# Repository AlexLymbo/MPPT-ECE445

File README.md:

# Senior Design Project(ECE445) - Custom Illini Solar Car MPPT
This project contains both the HW and FW for a boost converter MPPT made for the 3rd generation vehicle of Illini Solar Car. It utilizes a simple perturb and observe algorithm (P&O).

## More Info: 
The goal of this project was to develop custom and low cost solar Maximum Power Point Trackers (MPPTs). These MPPTs use a boost converter to optimize power output from the solar array to charge the battery efficiently. With the array divided into three sections for reliability, each MPPT gives redundancy to the system. Customization gives simple integration with the vehicle's electrical systems, allowing for plug-and-play functionality. This cost-effective solution takes away the need for expensive off-the-shelf components and provides access to schematics for easy maintenance and upgrades. 

https://www.youtube.com/watch?v=uG63rXX1FN4&t=2s

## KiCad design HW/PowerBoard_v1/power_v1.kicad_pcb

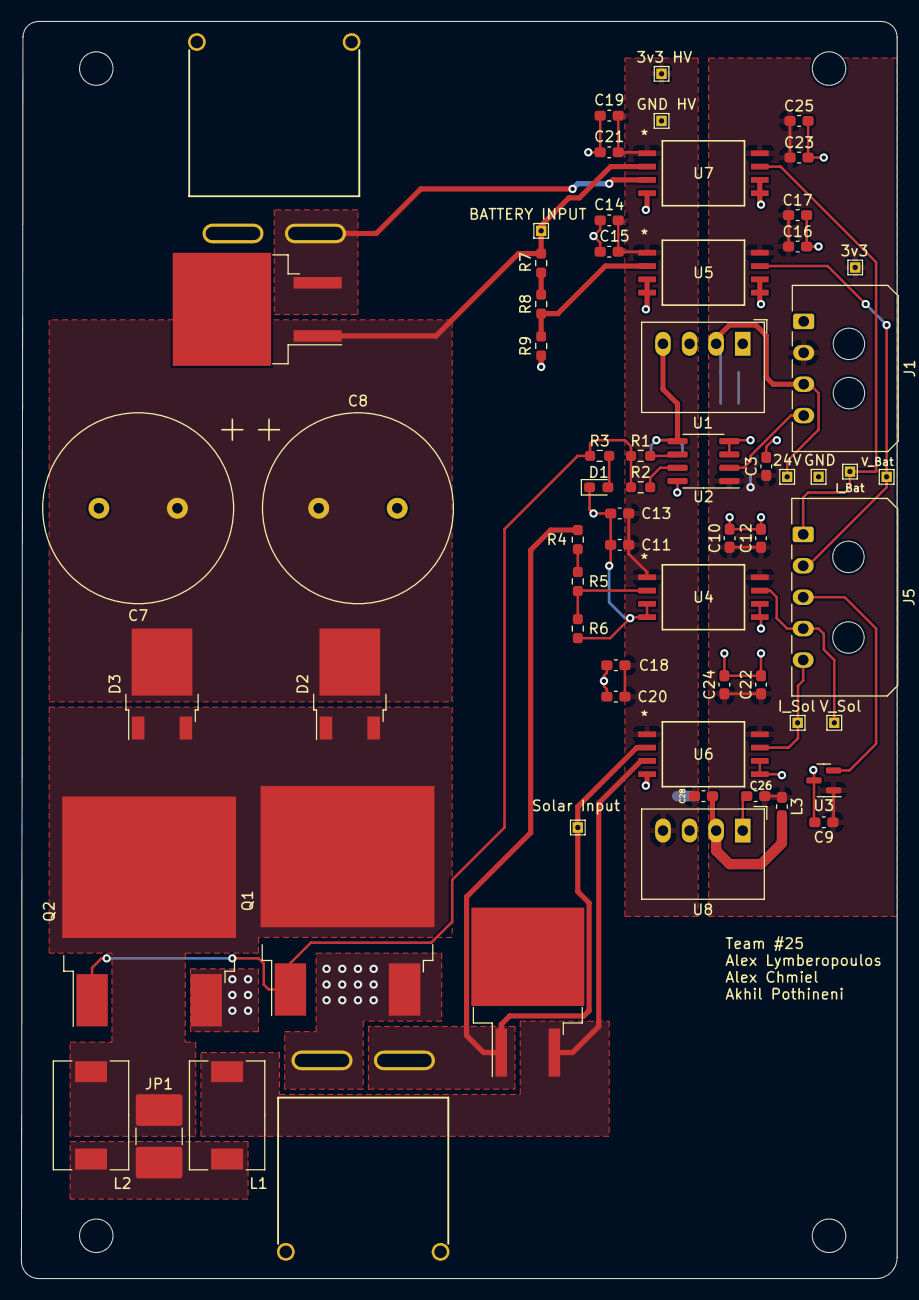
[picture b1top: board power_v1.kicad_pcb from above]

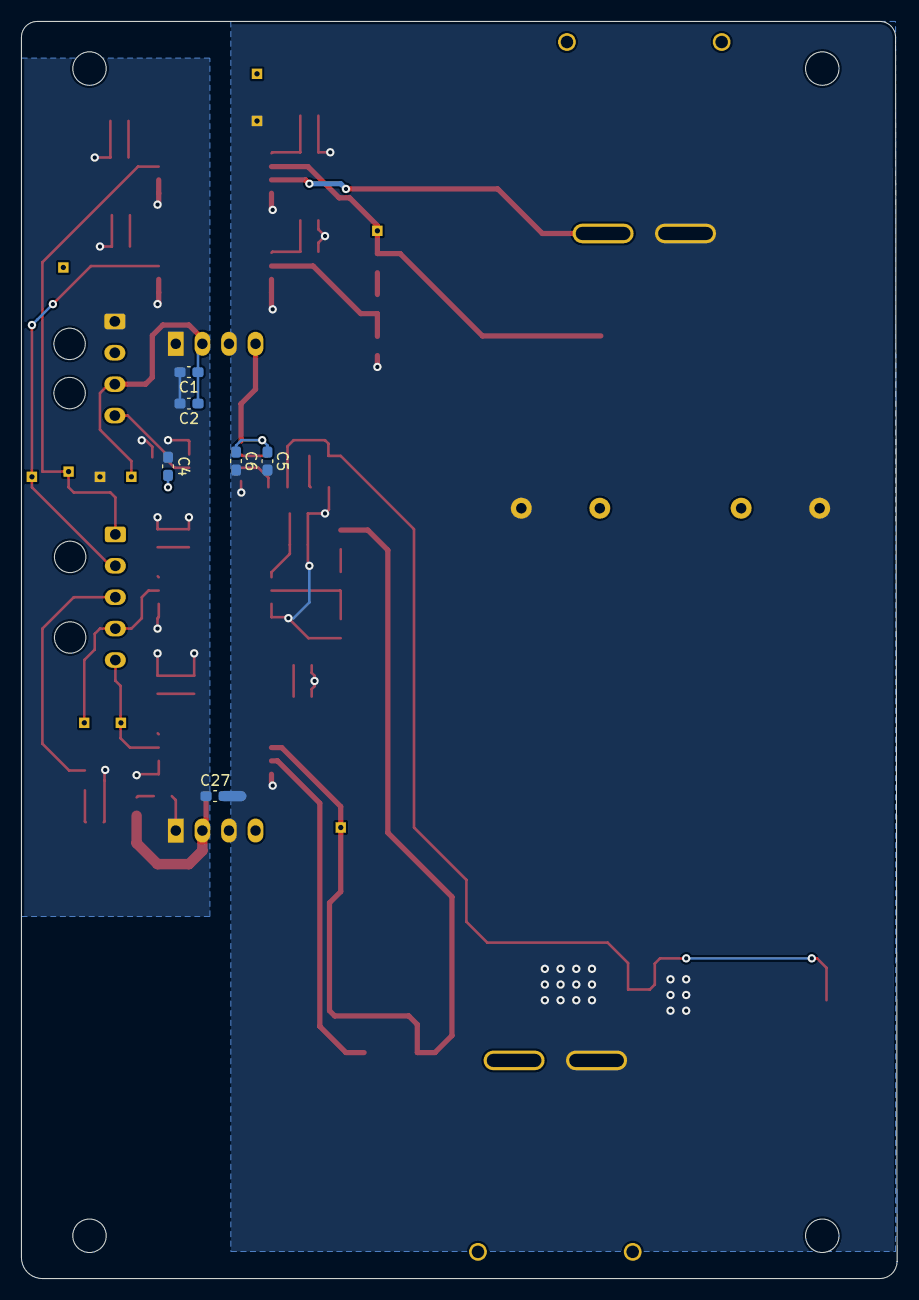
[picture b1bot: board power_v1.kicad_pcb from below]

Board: 2 copper layers, 83.6 x 120.1 mm, 75 parts (6 on the bottom side), 27 nets.

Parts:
C1, C26: 10uF; C_0603_1608Metric_Pad1.08x0.95mm_HandSolder
C2, C28: 1nF; C_0603_1608Metric_Pad1.08x0.95mm_HandSolder
C3, C4, C5, C6, C12, C13, C14, C17, C18, C19, C24, C25: 1uF; C_0603_1608Metric_Pad1.08x0.95mm_HandSolder
C7, C8: 470uF; C_Radial_D18.0mm_H35.5mm_P7.50mm
C9: 0.1uF; C_0603_1608Metric_Pad1.08x0.95mm_HandSolder
C10, C11, C15, C16, C20, C21, C22, C23: 100nF; C_0603_1608Metric_Pad1.08x0.95mm_HandSolder
C27: 2.2nF; C_0603_1608Metric_Pad1.08x0.95mm_HandSolder
D1: Blue; LED_0603_1608Metric_Pad1.05x0.95mm_HandSolder
D2, D3: 0.83V; TO-252-2
H1, H2, H3, H4: MountingHole; MountingHole_3.2mm_M3
J1: Inputs; Molex_Micro-Fit_3.0_43650-0400_1x04_P3.00mm_Horizontal
J3: Vin Solar; Anderson_Powerpole_45A_1x2_Horizontal_Bottom
J4: Vout Battery; Anderson_Powerpole_45A_1x2_Horizontal_Bottom
J5: Sensors; Molex_Micro-Fit_3.0_43650-0500_1x05_P3.00mm_Horizontal
JP1: SolderJumper_2_Open; R_2816_7142Metric
L1, L2: 1.2 μH; L_Wuerth_HCM-1050
L3: 22uH; L_0603_1608Metric_Pad1.05x0.95mm_HandSolder
Q1, Q2: IXTT220N20X4HV; TO-268-2
R1: 10; R_0603_1608Metric_Pad0.98x0.95mm_HandSolder
R2: 0; R_0603_1608Metric_Pad0.98x0.95mm_HandSolder
R3: 10k; R_0603_1608Metric_Pad0.98x0.95mm_HandSolder
R4, R5, R7, R8: 500k; R_0603_1608Metric_Pad0.98x0.95mm_HandSolder
R6: 53k; R_0603_1608Metric_Pad0.98x0.95mm_HandSolder
R9: 41.7k; R_0603_1608Metric_Pad0.98x0.95mm_HandSolder
R10, R11: 0.75; TO-263-2_isolatedback
TP1: +3V3A; TestPoint_THTPad_1.0x1.0mm_Drill0.5mm
TP2: GNDA; TestPoint_THTPad_1.0x1.0mm_Drill0.5mm
TP3: 24V; TestPoint_THTPad_1.0x1.0mm_Drill0.5mm
TP4: GND; TestPoint_THTPad_1.0x1.0mm_Drill0.5mm
TP5: 3V3; TestPoint_THTPad_1.0x1.0mm_Drill0.5mm
TP6: ADC V Sol; TestPoint_THTPad_1.0x1.0mm_Drill0.5mm
TP7, TP11: ADC V Batt; TestPoint_THTPad_1.0x1.0mm_Drill0.5mm
TP8: ADC I Sol; TestPoint_THTPad_1.0x1.0mm_Drill0.5mm
TP9, TP13: ADC I Batt; TestPoint_THTPad_1.0x1.0mm_Drill0.5mm
U1: RO-2412S; Converter_DCDC_RECOM_R-78S-0.1_THT
U2: STGAP2SMTR; SOIC-8_3.9x4.9mm_P1.27mm
U3: MCP9700AT-ETT; SOT-23
U4, U5, U6, U7: PAMC1350DWVR; U_PAMC1350DWVR_TEX
U8: 3v3 ISO DC/DC; Converter_DCDC_RECOM_R-78S-0.1_THT

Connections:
+3.3VA: C11.1, C13.1, C14.1, C15.1, C18.1, C19.1, C20.1, C21.1, C28.1, TP1.1, U4.1 (VDD1), U5.1 (VDD1), U6.1 (VDD1), U7.1 (VDD1), U8.4 (+VOUT)
+3V3: C3.1, C4.1, C9.1, C10.1, C12.1, C16.1, C17.1, C22.1, C23.1, C24.1, C25.1, C26.1, J1.2, L3.1, TP5.1, U2.1 (VDD), U3.1 (Vdd), U4.8 (VDD2), U5.8 (VDD2), U6.8 (VDD2), U7.8 (VDD2)
+24V: C1.1, C2.1, J1.3, TP3.1, U1.2 (+VIN)
/ADC I Batt: J5.1, TP9.1, U7.7 (OUTP)
/ADC I Sol: J5.5, TP8.1, U6.7 (OUTP)
/ADC V Batt: J5.2, TP7.1, U5.7 (OUTP)
/ADC V Sol: J5.4, TP6.1, U4.7 (OUTP)
/Batt In: C7.1, C8.1, D2.2 (K), D3.2 (K), R7.1, R11.1, TP11.1, U7.2 (INP)
/Batt Out: J4.1, R11.2, U7.3 (INN)
/Board Temp: J5.3, U3.2 (Vout)
/DNP Anode: D2.1 (A), D2.3 (A), D3.1 (A), D3.3 (A), JP1.2 (B), L2.2, Q1.2 (D), Q2.2 (D)
/Gate: Q1.1 (G), Q2.1 (G), R1.1, R2.1, R3.1
/PWM: J1.4, U2.2 (IN+)
/SW_G+: R1.2, U2.6 (GON)
/SW_G-: R2.2, U2.7 (GOFF)
/Sensors/V Sense Batt: R8.2, R9.1, U5.2 (INP)
/Sensors/V Sense Sol: R5.2, R6.1, U4.2 (INP)
/Sol In: J3.2, R4.1, R10.1, TP13.1, U6.2 (INP)
/Sol Out: L1.1, R10.2, U6.3 (INN)
Earth: C5.2, C6.2, C7.2, C8.2, C11.2, C13.2, C14.2, C15.2, C18.2, C19.2, C20.2, C21.2, C27.2, D1.1 (K), J3.1, J4.2, Q1.3 (S), Q2.3 (S), R6.2, R9.2, TP2.1, U1.3 (-VOUT), U2.8 (GNDISO), U4.3 (INN), U4.4 (GND1), U5.3 (INN), U5.4 (GND1), U6.4 (GND1), U7.4 (GND1), U8.3 (-VOUT)
GND: C1.2, C2.2, C3.2, C4.2, C9.2, C10.2, C12.2, C16.2, C17.2, C22.2, C23.2, C24.2, C25.2, C26.2, C27.1, J1.1, TP4.1, U1.1 (-VIN), U2.3 (IN-), U2.4 (GND), U3.3 (GND), U4.5 (GND2), U4.6 (OUTN), U5.5 (GND2), U5.6 (OUTN), U6.5 (GND2), U6.6 (OUTN), U7.5 (GND2), U7.6 (OUTN), U8.1 (-VIN)
unnamed: D1.2 (A), R3.2
unnamed: JP1.1 (A), L1.2, L2.1
unnamed: R4.2, R5.1
unnamed: R7.2, R8.1
unnamed: C5.1, C6.1, U1.4 (+VOUT), U2.5 (VH)
unnamed: C28.2, L3.2, U8.2 (+VIN)

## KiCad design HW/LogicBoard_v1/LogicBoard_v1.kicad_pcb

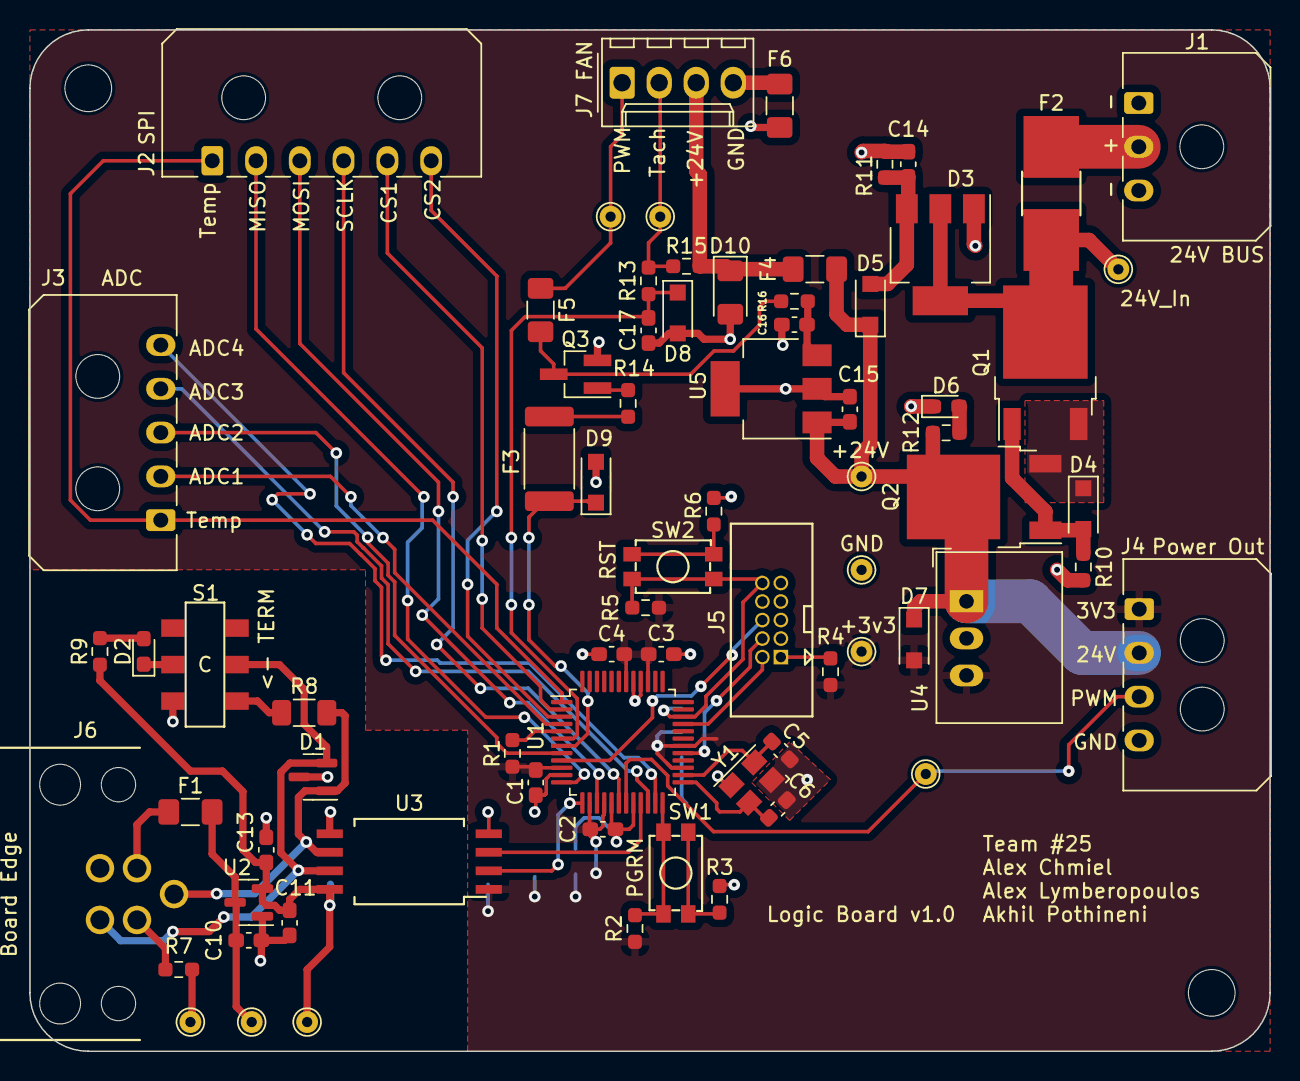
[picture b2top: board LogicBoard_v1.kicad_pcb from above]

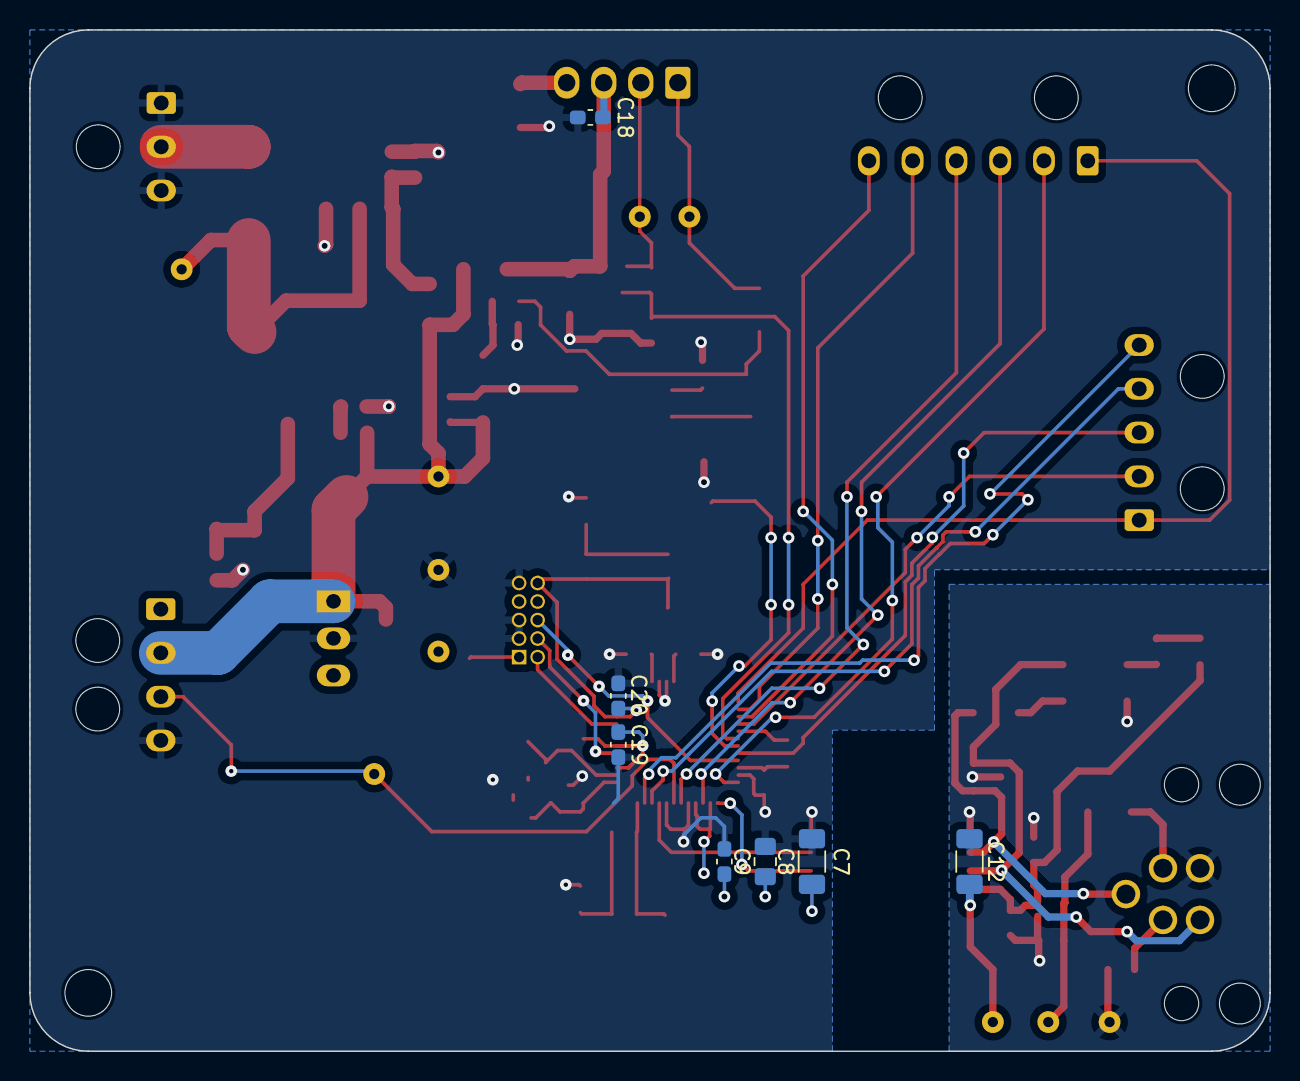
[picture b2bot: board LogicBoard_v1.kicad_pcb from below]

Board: 2 copper layers, 85.0 x 70.0 mm, 83 parts (7 on the bottom side), 53 nets.

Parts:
C1, C2, C3, C4, C9, C10, C11, C13, C15, C17, C19, C20: 0.1uF; C_0603_1608Metric_Pad1.08x0.95mm_HandSolder
C5, C6: 18pF; C_0603_1608Metric_Pad1.08x0.95mm_HandSolder
C7, C12: 10uF; C_1206_3216Metric_Pad1.33x1.80mm_HandSolder
C8: 1uF; C_0805_2012Metric_Pad1.18x1.45mm_HandSolder
C14: 0.047u; C_0603_1608Metric_Pad1.08x0.95mm_HandSolder
C16: 10uF; C_0603_1608Metric_Pad1.08x0.95mm_HandSolder
C18: 1uF; C_0603_1608Metric_Pad1.08x0.95mm_HandSolder
D1: PESD1CAN; SOT-23
D2: Yellow; LED_0603_1608Metric_Pad1.05x0.95mm_HandSolder
D3: Q_SCR_KAG; SOT-223-3_TabPin2
D4: 20 V; D_SOD-123F
D5: 28 V; D_SOD-123F
D6: LED; LED_0603_1608Metric_Pad1.05x0.95mm_HandSolder
D7: D_Schottky; D_SOD-123F
D8, D9: 3V6; D_SOD-123F
D10: 40V 2A; D_1206_3216Metric_Pad1.42x1.75mm_HandSolder
F1: 0.2A; Fuse_1206_3216Metric_Pad1.42x1.75mm_HandSolder
F2: 5A; Littelfuse_154_4.24mm_x_3.81mm
F3: 100mA; Fuse_2512_6332Metric
F4: 0.25A Fuse; Fuse_1206_3216Metric_Pad1.42x1.75mm_HandSolder
F5: 0.2A Fuse; Fuse_1206_3216Metric_Pad1.42x1.75mm_HandSolder
F6: 1A Fuse; Fuse_1206_3216Metric_Pad1.42x1.75mm_HandSolder
H1, H2: MountingHole; MountingHole_3.2mm_M3
J1: 24V In; Molex_Micro-Fit_3.0_43650-0300_1x03_P3.00mm_Horizontal
J2: Comm; Molex_Micro-Fit_3.0_43650-0600_1x06_P3.00mm_Horizontal
J3: ADC; Molex_Micro-Fit_3.0_43650-0500_1x05_P3.00mm_Horizontal
J4: Power; Molex_Micro-Fit_3.0_43650-0400_1x04_P3.00mm_Horizontal
J5: JTAG_Header; IDC-Header_2x05_Pitch1.27mm_Straight
J6: CAN; M12_5-pin_90deg_VertPitch2.54mm
J7: Fans; Molex_KK-254_AE-6410-04A_1x04_P2.54mm_Vertical
Q1, Q2: Q_PMOS_GDS; TO-252-2
Q3: Q_NMOS_GSD; SOT-23_Handsoldering
R1, R2, R5, R11, R12, R13, R15: 10k; R_0603_1608Metric_Pad0.98x0.95mm_HandSolder
R3, R6, R9, R10: 1k; R_0603_1608Metric_Pad0.98x0.95mm_HandSolder
R4: 0; R_0603_1608Metric_Pad0.98x0.95mm_HandSolder
R7: 1M; R_0603_1608Metric_Pad0.98x0.95mm_HandSolder
R8: 120; R_1206_3216Metric_Pad1.30x1.75mm_HandSolder
R14: 500; R_0603_1608Metric_Pad0.98x0.95mm_HandSolder
R16: 10K; R_0603_1608Metric_Pad0.98x0.95mm_HandSolder
S1: CL-SB-22B-01; DPDT_NIDEC_6_pin_SMD_1.6_x_1.2_pads
SW1: ISP; Button_223AM
SW2: ~RESET; Button_223AM
TP1: Duty PWM; TestPoint_THTPad_D1.5mm_Drill0.7mm
TP2: CAN_VCC_Fused; TestPoint_THTPad_D1.5mm_Drill0.7mm
TP3: GND_CAN; TestPoint_THTPad_D1.5mm_Drill0.7mm
TP4: +5V_CAN; TestPoint_THTPad_D1.5mm_Drill0.7mm
TP5: 24V IN; TestPoint_THTPad_D1.5mm_Drill0.7mm
TP6: GND; TestPoint_THTPad_D1.5mm_Drill0.7mm
TP7: 24V OUT; TestPoint_THTPad_D1.5mm_Drill0.7mm
TP8: 3v3; TestPoint_THTPad_D1.5mm_Drill0.7mm
TP9: Tach; TestPoint_THTPad_D1.5mm_Drill0.7mm
TP10: Fan PWM; TestPoint_THTPad_D1.5mm_Drill0.7mm
U1: LPC1547JBD48; LQFP-48_7x7mm_P0.5mm
U2: MCP1754S-5002E_SOT23A; SOT-23
U3: ISO1042DWV; SOIC-8_5.85x7.4mm_P1.27mm
U4: R-783.3-0.5; Converter_DCDC_RECOM_R-78E-0.5_THT
U5: BD450M2FP3-CE2; SOT-223-3_TabPin2
Y1: 12MHz; Crystal_SMD_TXC_7M-4pin_3.2x2.5mm

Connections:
+3V3: C1.1, C2.1, C3.1, C4.1, C7.1, C8.1, C9.1, C19.1, D7.2 (A), J4.1, R1.1, R2.1, R4.1, R5.2, TP8.1, U1.10 (VREFP_ADC), U1.14 (VREFP_DAC_VDDCMP), U1.16 (VDDA), U1.27 (VDD), U1.30 (VBAT), U1.39 (VDD), U1.42 (VDD), U3.1 (Vcc1), U4.3 (OUT)
+5V: C16.1, R16.1, U5.3 (VO)
+24V: C15.1, D5.1 (K), D7.1 (K), F4.1, J4.2, Q2.2 (D), R12.1, TP7.1, U4.1 (IN), U5.1 (VI)
/CAN/+5V_CAN: C11.1, C12.1, C13.1, R9.2, TP4.1, U2.2 (VO), U3.8 (Vcc2)
/CAN/CANH: D1.2 (K), J6.4, S1.5, U3.7 (CANH)
/CAN/CANL: D1.1 (K), J6.5, R8.2, U3.6 (CANL)
/CAN/CAN_RX: U1.21 (PIO0_13/ADC1_6), U3.3 (RXD)
/CAN/CAN_Shield: J6.1, R7.2
/CAN/CAN_TX: U1.13 (PIO0_18/SCT0_OUT5), U3.2 (TXD)
/CAN/CAN_VCC_Fused: C10.1, F1.1, TP2.1, U2.3 (VI)
/CAN/CAN_VCC_Unfused: F1.2, J6.2
/CAN/GND_CAN: C10.2, C11.2, C12.2, C13.2, D1.3 (A), J6.3, R7.1, S1.3, TP3.1, U2.1 (GND), U3.5 (GND2)
/CAN/TERM_LED: D2.1 (K), S1.2
/Fans/24V_fused: C18.1, D10.1 (K), F4.2, J7.3, R15.1
/Fans/Fan_PWM: D9.1 (K), F3.2, U1.7 (PIO0_6/ADC0_2/SCT2_OUT3)
/Fans/Fan_Tach: C17.2, D8.1 (K), R13.1, U1.6 (PIO0_5/ADC0_3)
/Fans/PWM_5V: F5.2, Q3.3 (D), R16.2
/Fans/Tach: J7.2, R13.2, R15.2, TP9.1
/MCU/ADC_1: J3.2, U1.4 (PIO0_3/ADC0_5/SCT1_OUT4)
/MCU/ADC_2: J3.3, U1.8 (PIO0_7/ADC0_1)
/MCU/ADC_3: J3.4, U1.22 (PIO0_14/ADC1_7/SCT1_OUT5)
/MCU/ADC_4: J3.5, U1.23 (PIO0_15/ADC1_8)
/MCU/CS_1: J2.5, U1.2 (PIO0_1/ADC0_7/SCT0_OUT4)
/MCU/CS_2: J2.6, U1.3 (PIO0_2/ADC0_6/SCT1_OUT3)
/MCU/ISP0: R1.2, U1.5 (PIO0_4/ADC0_4)
/MCU/ISP1: R2.2, SW1.1, U1.24 (PIO0_16/ADC1_9)
/MCU/MISO: J2.2, U1.12 (PIO0_9/ADC1_1/TDI)
/MCU/MOSI: J2.3, U1.15 (PIO0_10/ADC1_2)
/MCU/PWM: J4.3, TP1.1, U1.19 (PIO0_12/DAC_OUT)
/MCU/RESET: C20.1, J5.10 (~RESET), R5.1, SW2.1, U1.34 (~RESET/PIO0_21)
/MCU/SCLK: J2.4, U1.18 (PIO0_11/ADC1_3)
/MCU/TCLK: J5.4 (TCLK), U1.29 (SWCLK/PIO0_19/TCK)
/MCU/TMS: J5.2 (TMS), U1.33 (SWDIO/PIO0_20/SCT1_OUT6/TMS)
/MCU/Temp_Sens_ADC: J2.1, J3.1, U1.1 (PIO0_0/ADC0_10/SCT0_OUT3)
/Power/24V_Unprotected: F2.2, J1.2
/Power/+24V_FUSED: D3.2 (A), F2.1, Q1.2 (D), TP5.1
GND: C1.2, C2.2, C3.2, C4.2, C5.1, C6.1, C7.2, C8.2, C9.2, C14.2, C15.2, C16.2, C17.1, C18.2, C19.2, C20.2, D3.1 (K), D6.1 (K), D8.2 (A), D9.2 (A), D10.2 (A), F6.2, J1.1, J1.3, J4.4, J5.3 (GND), J5.5 (GND), J5.9 (GND), Q3.2 (S), R3.1, R6.1, R10.2, R11.2, TP6.1, U1.11 (VREFN), U1.17 (VSSA), U1.20 (VSS), U1.40 (VSS), U1.41 (VSS), U3.4 (GND1), U4.2 (GND), U5.2 (GND), Y1.2, Y1.4
unnamed: D2.2 (A), R9.1
unnamed: C14.1, D3.3 (G), D5.2 (A), R11.1
unnamed: D4.2 (A), Q1.1 (G), Q2.1 (G), R10.1
unnamed: D4.1 (K), Q1.3 (S), Q2.3 (S)
unnamed: D6.2 (A), R12.2
unnamed: F3.1, R14.2
unnamed: J5.6 (TDO), U1.9 (PIO0_8/ADC0_0/TDO)
unnamed: J5.1 (VCC), R4.2
unnamed: F5.1, J7.1, TP10.1
unnamed: F6.1, J7.4
unnamed: Q3.1 (G), R14.1
unnamed: R3.2, SW1.2
unnamed: R6.2, SW2.2
unnamed: R8.1, S1.6
unnamed: C5.2, U1.26 (XTALIN), Y1.1
unnamed: C6.2, U1.25 (XTALOUT), Y1.3

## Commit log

2024-02-22 init commit with spice sim
2024-02-22 init hardware stuff
2024-02-22 added gitignore
2024-02-22 fixed non necessary files
2024-02-22 more changes
2024-02-22 boost added to power board
2024-02-22 cleaned up schematic
2024-02-22 update sim to simulate array better
2024-02-22 updated the thing
2024-02-23 Started logic board
2024-02-27 Finsihed logic board schematic
2024-03-01 updates sensing
2024-03-04 updated sensing portion
2024-03-05 added resistors for sensing
2024-03-05 small visual changes
2024-03-05 added resistor values for voltage sense
2024-03-05 finished schematic
2024-03-05 error fixing
2024-03-05 updated naming
2024-03-05 name changes
2024-03-05 small layout changes
2024-03-05 need to figure out current sense res fp
2024-03-05 more layout
2024-03-05 added changes
2024-03-05 pushed board
2024-03-19 Almost done with logic board
2024-03-19 Finsihed logic board
2024-03-19 gerbers
2024-03-21 added ti paper for resistor sizing
2024-03-28 pushed changes
2024-04-02 added excel
2024-04-07 Sensor Data
2024-04-07 renamed FW
2024-04-07 new FW stuff
2024-04-07 updates to FW for duty cycle control
2024-04-10 added init MPPT changes
2024-04-15 updates to FW
2024-04-16 updated to add battery voltage measurement
2024-04-16 added upper and lower limits of duty request
2024-04-21 pushed FW
2024-04-22 something happened
